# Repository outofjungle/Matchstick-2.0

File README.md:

# Matchstick 2.0

## Schematic

## Top

## Bottom

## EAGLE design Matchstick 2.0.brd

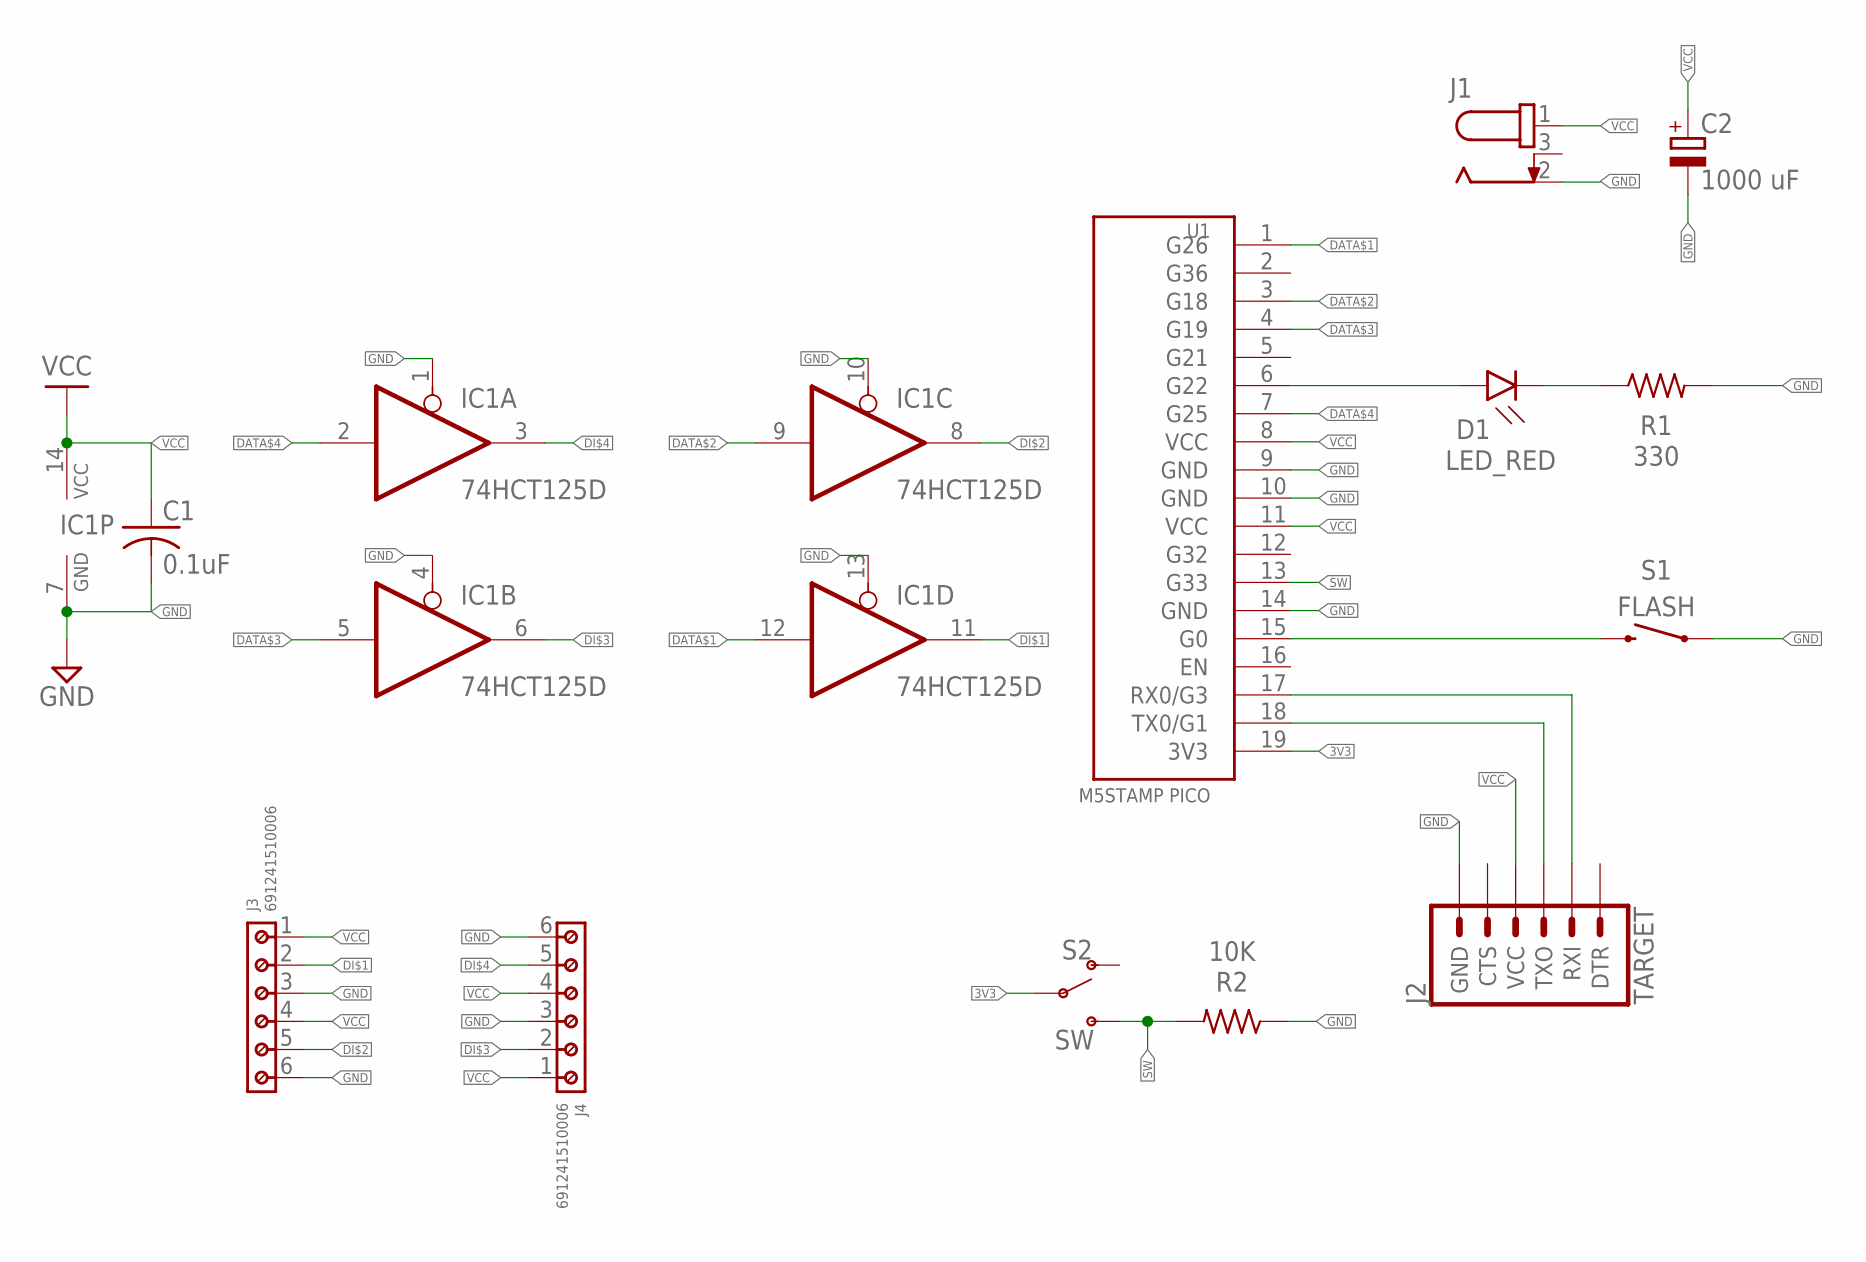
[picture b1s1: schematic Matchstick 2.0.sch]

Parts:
C1: 0.1uF; CAPC2012X110
C2: 1000 uF; CAPPRD508W65D1000H1100B
D1: LED_RED; LEDC2012X110N_FLAT-R
IC1: 74HCT125D; SO14
J1: 694106301002
J2: TARGET; 6_PIN_SERIAL_TARGET_SIDE_W_SILK
J3, J4: 691241510006
R1: 330; RESC2012X65
R2: 10K; RESC2012X65
S1: FLASH; TACTILE_SWITCH_SMD_5.2MM
S2: SW; SWITCH_SPST_SMD_A
U1: M5STAMP PICO; M5STAMP-PICO

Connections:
3V3: S2.2, U1.19 (3V3)
DATA$1: IC1.12 (I), U1.1 (G26)
DATA$2: IC1.9 (I), U1.3 (G18)
DATA$3: IC1.5 (I), U1.4 (G19)
DATA$4: IC1.2 (I), U1.7 (G25)
DI$1: IC1.11 (O), J3.2
DI$2: IC1.8 (O), J3.5
DI$3: IC1.6 (O), J4.2
DI$4: IC1.3 (O), J4.5
G0: S1.3 (2), U1.15 (G0)
GND: C1.2, C2.2 (-), IC1.1 (OE), IC1.4 (OE), IC1.7 (GND), IC1.10 (OE), IC1.13 (OE), J1.2, J2.P$6 (GND), J3.3, J3.6, J4.3, J4.6, R1.2, R2.1, S1.1, U1.9 (GND), U1.10 (GND), U1.14 (GND)
RX: J2.P$3 (RXI), U1.17 (RX0/G3)
SATUS_LED$1: D1.A, U1.6 (G22)
SATUS_LED$2: D1.C, R1.1
SW: R2.2, S2.3 (S), U1.13 (G33)
TX: J2.P$2 (TXO), U1.18 (TX0/G1)
VCC: C1.1, C2.1 (+), IC1.14 (VCC), J1.1, J2.P$4 (VCC), J3.1, J3.4, J4.1, J4.4, U1.8 (VCC), U1.11 (VCC)

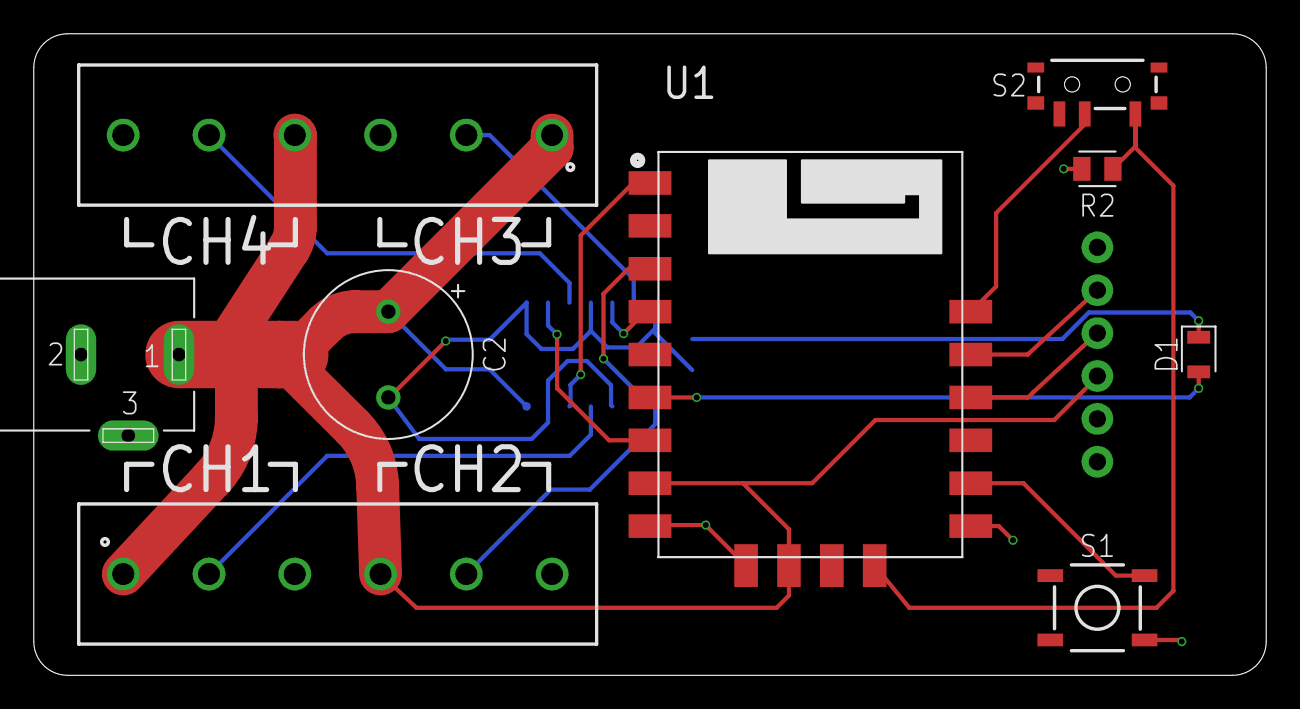
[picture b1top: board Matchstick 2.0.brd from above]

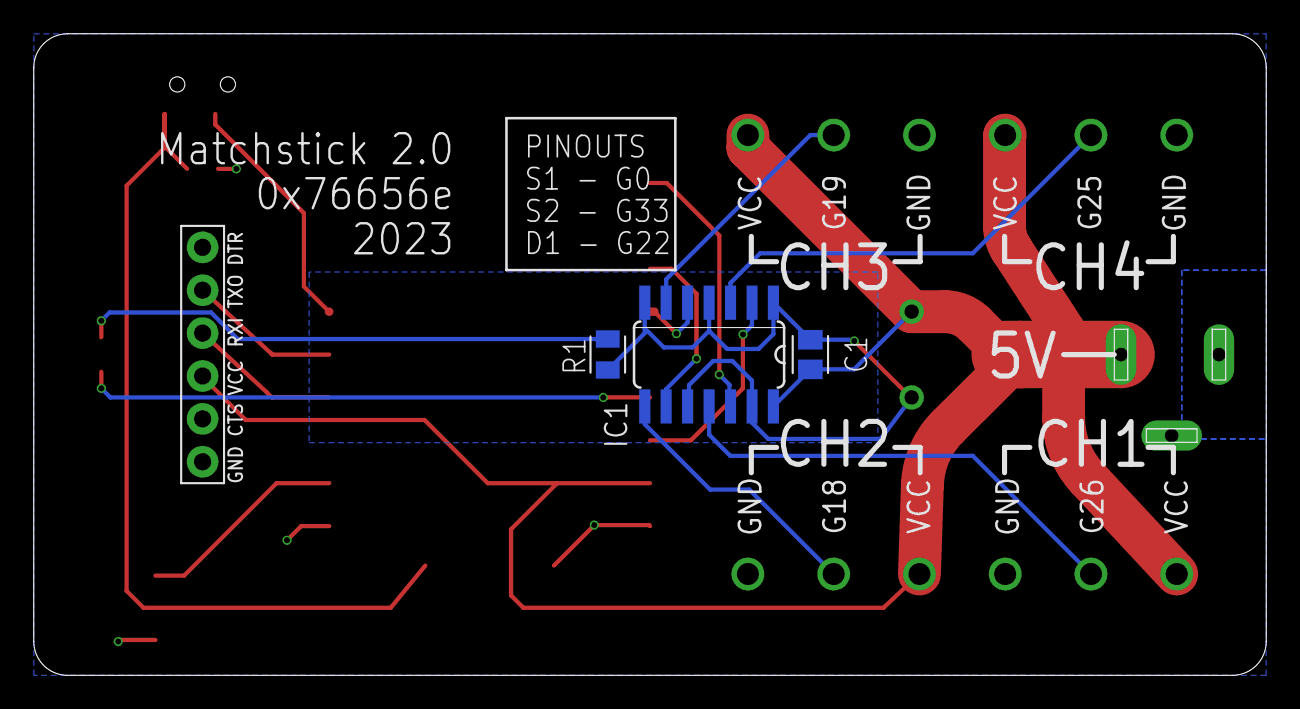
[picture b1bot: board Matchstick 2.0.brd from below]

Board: 2 copper layers, 73.0 x 38.0 mm, 13 parts (4 on the bottom side), 17 nets.

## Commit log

2023-10-26 inital commit of matchstick 2.0
2023-10-26 adding rendering of the PCB
2023-10-26 updated silk screen
2023-10-26 fixing thermal reliefs
2023-10-26 adjusting traces for solderability
2023-10-26 adding silkscreen documenation
2023-10-26 more silkscreen markings
2023-10-26 tenting the vias
2023-10-26 fix few alignment issues
2023-10-26 changed signal traces to 0.254mm
2023-10-27 fixing the crossed signals
2023-10-27 fixing the crossed signals 2
2023-10-27 updated images
2023-10-27 redoing silk screen
2023-10-27 save - no clue
2023-10-29 updated readme with schematic
2023-10-30 cosmetic changes
2023-10-30 bigger schematic
2023-10-31 Adding gerber files

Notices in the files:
parts and their libraries:
Wurth_Connectors_WR-TBL Rising Cage Clam: Copyright: Würth Elektronik
SparkFun-Switches: Licensing: Creative Commons ShareAlike 4.0 International - https://creativecommons.org/licenses/by-sa/4.0
